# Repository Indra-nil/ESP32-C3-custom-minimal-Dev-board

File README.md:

# ESP32-C3 custom minimal Dev board

This board based on ESP32-C3-MINI-1. To reduce power consumption for battery operations and PCB dimension, dedicated USB to UART converter not used. The USB directly connected to Serial/JTAG controller of ESP32-C3 (GPIO18 and GPIO19). This can be used as CDC-ACM virtual serial port, programming embedded/external flash, CPU debugging with compact JTAG instructions.

### The power jumper should shorted with a shunt for normal operations. This pins are helpful for measuring current consumption (fast switching currents) using power analyzers(PPK2, Otii Arc etc).

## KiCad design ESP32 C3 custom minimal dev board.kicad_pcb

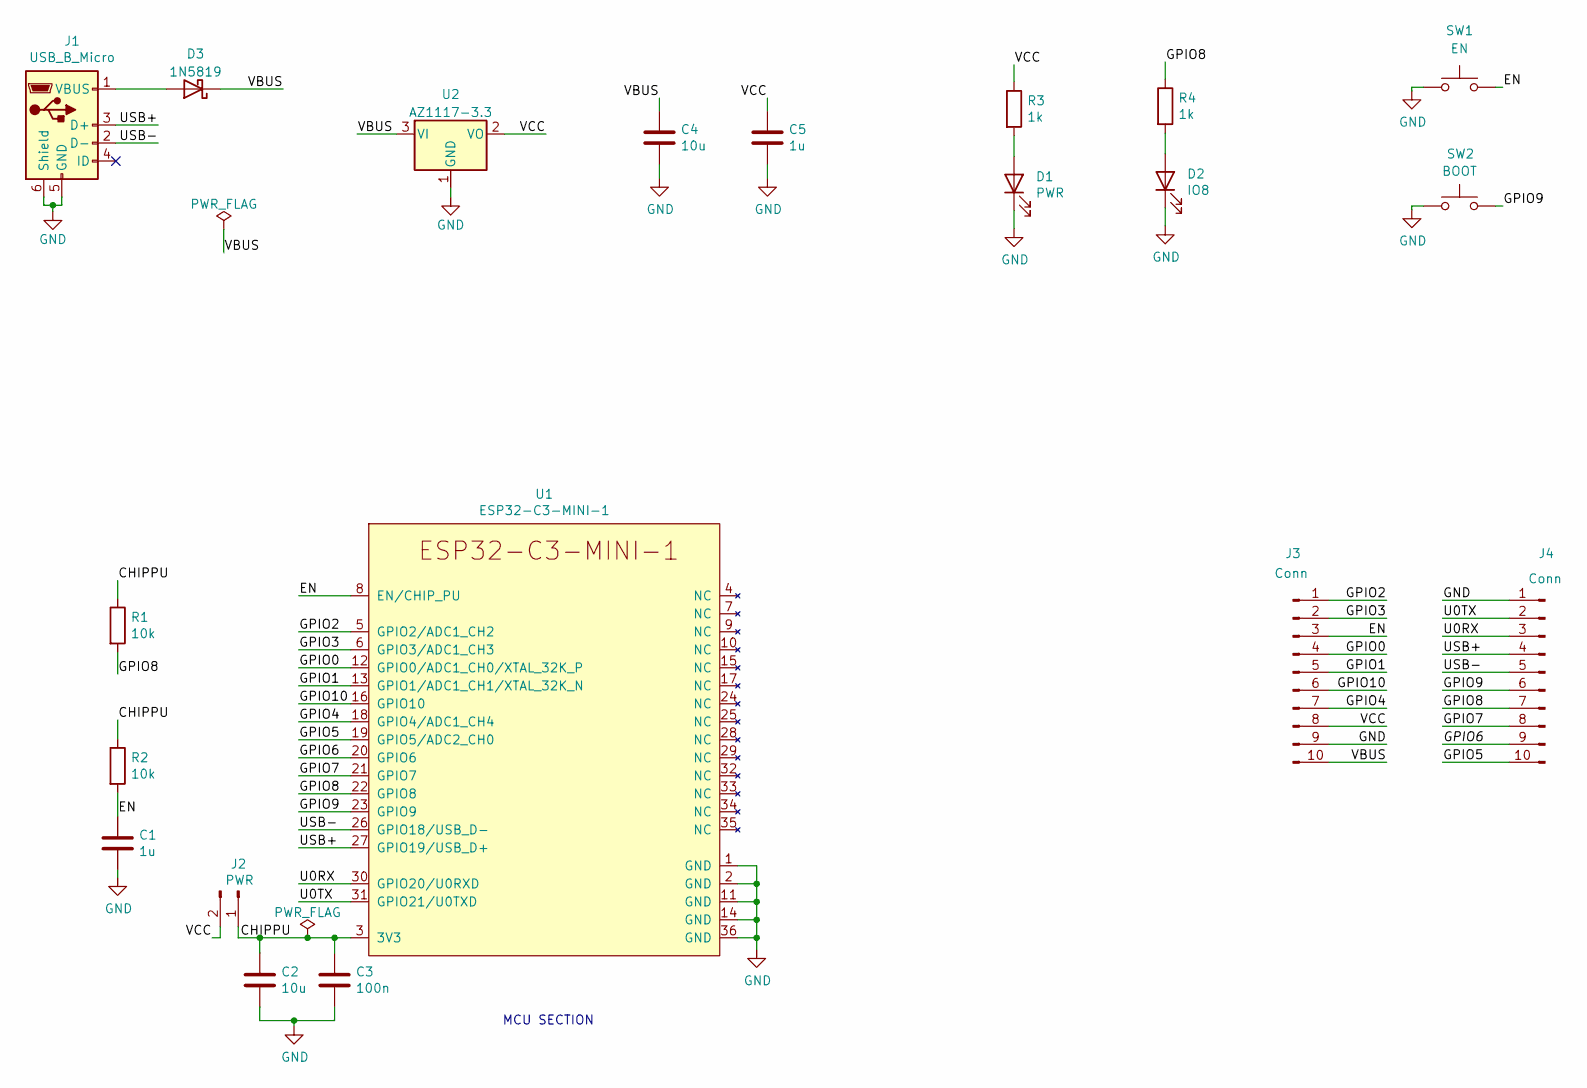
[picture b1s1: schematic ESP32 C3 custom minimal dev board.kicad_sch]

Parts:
C1, C5: 1u; C_0603_1608Metric
C2, C4: 10u; C_0805_2012Metric
C3: 100n; C_0603_1608Metric
D1: PWR; LED_0603_1608Metric
D2: IO8; LED_0603_1608Metric
D3: 1N5819; D_SOD-123
J1: USB_B_Micro; MUP-U513
J2: PWR; PinHeader_1x02_P2.54mm_Vertical
J3, J4: Conn; PinHeader_1x10_P2.54mm_Vertical
R1, R2: 10k; R_0603_1608Metric
R3, R4: 1k; R_0603_1608Metric
SW1: EN; SW_Push_SPST_NO_Alps_SKRK
SW2: BOOT; SW_Push_SPST_NO_Alps_SKRK
U1: ESP32-C3-MINI-1
U2: AZ1117-3.3; SOT-89-3

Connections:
/CHIPPU: C2.1, C3.1, J2.1, R1.1, R2.1, U1.3 (3V3)
/EN: C1.1, J3.3, R2.2, SW1.2, U1.8 (EN/CHIP_PU)
/GPIO0: J3.4, U1.12 (GPIO0/ADC1_CH0/XTAL_32K_P)
/GPIO1: J3.5, U1.13 (GPIO1/ADC1_CH1/XTAL_32K_N)
/GPIO2: J3.1, U1.5 (GPIO2/ADC1_CH2)
/GPIO3: J3.2, U1.6 (GPIO3/ADC1_CH3)
/GPIO4: J3.7, U1.18 (GPIO4/ADC1_CH4)
/GPIO5: J4.10, U1.19 (GPIO5/ADC2_CH0)
/GPIO6: J4.9, U1.20 (GPIO6)
/GPIO7: J4.8, U1.21 (GPIO7)
/GPIO8: J4.7, R1.2, R4.1, U1.22 (GPIO8)
/GPIO9: J4.6, SW2.2, U1.23 (GPIO9)
/GPIO10: J3.6, U1.16 (GPIO10)
/U0RX: J4.3, U1.30 (GPIO20/U0RXD)
/U0TX: J4.2, U1.31 (GPIO21/U0TXD)
/USB+: J1.3 (D+), J4.4, U1.27 (GPIO19/USB_D+)
/USB-: J1.2 (D-), J4.5, U1.26 (GPIO18/USB_D-)
/VBUS: C4.1, D3.1 (K), J3.10, U2.3 (VI)
/VCC: C5.1, J2.2, J3.8, R3.1, U2.2 (VO)
GND: C1.2, C2.2, C3.2, C4.2, C5.2, D1.1 (K), D2.1 (K), J1.5 (GND), J1.6 (Shield), J3.9, J4.1, SW1.1, SW2.1, U1.1 (GND), U1.2 (GND), U1.11 (GND), U1.14 (GND), U1.36 (GND), U2.1 (GND)
unnamed: D1.2 (A), R3.2
unnamed: D2.2 (A), R4.2
unnamed: D3.2 (A), J1.1 (VBUS)

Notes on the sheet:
MCU SECTION

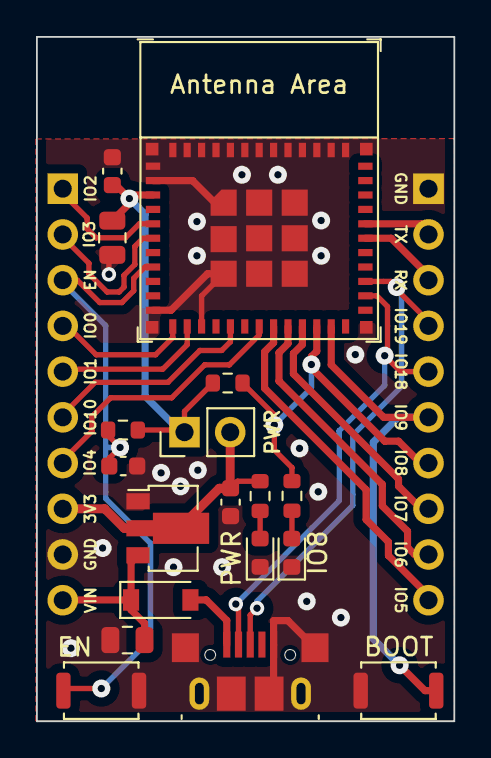
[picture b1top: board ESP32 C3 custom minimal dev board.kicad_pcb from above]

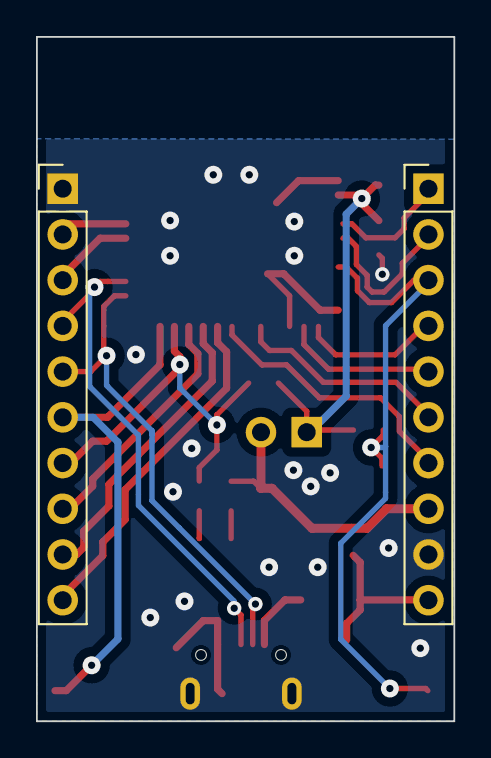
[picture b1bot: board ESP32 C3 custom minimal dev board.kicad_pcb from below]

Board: 2 copper layers, 23.2 x 38.0 mm, 20 parts (2 on the bottom side), 23 nets.

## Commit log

2022-05-12 Initial release
